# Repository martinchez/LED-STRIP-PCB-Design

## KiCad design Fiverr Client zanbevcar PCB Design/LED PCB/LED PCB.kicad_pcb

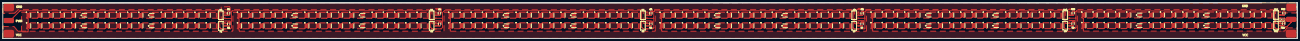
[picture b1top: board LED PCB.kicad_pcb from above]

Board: 2 copper layers, 980.4 x 27.1 mm, 235 parts (0 on the bottom side), 219 nets.

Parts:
J1, J3, J4, J6: Conn_01x01; power pad
J2, J5: Conn_01x01; signal pad
LED1, LED2, LED3, LED4, LED5, LED6, LED7, LED8, LED9, LED10, LED11, LED12, LED13, LED14, LED16, LED17, LED18, LED19, LED20, LED21, LED22, LED23, LED24, LED25, LED26, LED27, LED28, LED29, LED30, LED31, LED32, LED33, LED34, LED35, LED36, LED37, LED38, LED39, LED40, LED41, LED42, LED43, LED44, LED45, LED46, LED47, LED48, LED49, LED50, LED51, LED52, LED53, LED54, LED55, LED56, LED57, LED58, LED59, LED60, LED73, LED74, LED75, LED76, LED77, LED78, LED79, LED80, LED81, LED82, LED83, LED84, LED85, LED86, LED87, LED88, LED89, LED90, LED91, LED92, LED93, LED94, LED95, LED96, LED97, LED98, LED99, LED100, LED101, LED102, LED103, LED104, LED105, LED106, LED107, LED108, LED109, LED110, LED111, LED112, LED113, LED114, LED115, LED116, LED117, LED118, LED119, LED120, LED121, LED122, LED123, LED124, LED125, LED126, LED127, LED128, LED129, LED130, LED131, LED132, LED145, LED146, LED147, LED148, LED149, LED150, LED151, LED152, LED153, LED154, LED155, LED156, LED157, LED158, LED159, LED160, LED161, LED162, LED163, LED164, LED165, LED166, LED167, LED168, LED169, LED170, LED171, LED172, LED173, LED174, LED175, LED176, LED177, LED178, LED179, LED180, LED181, LED182, LED183, LED184, LED185, LED186, LED187, LED188, LED189, LED190, LED191, LED192, LED193, LED194, LED195, LED196, LED197, LED198, LED199, LED200, LED201, LED202, LED203, LED204: SPMWHD32AMH5XAU5SL
LED61, LED62, LED63, LED64, LED65, LED66, LED67, LED68, LED69, LED70, LED71, LED72, LED133, LED134, LED135, LED136, LED137, LED138, LED139, LED140, LED141, LED142, LED143, LED144: L1SP-DRD0002800000
LEDe: SPMWHD32AMH5XAU5SL
R1, R2, R3, R4, R5, R6, R7, R8, R9, R10, R11, R12: 5.6R; R_1206_3216Metric
U1, U2, U3, U4, U5, U6, U7, U8, U9, U10, U11, U12: NCR321ZX
kibuzzard-6473B6E2: G***; kibuzzard-6473B6E2

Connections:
GND: J3.1, J6.1, R1.2, R2.2, R3.2, R4.2, R5.2, R6.2, R7.2, R8.2, R9.2, R10.2, R11.2, R12.2, U1.3 (GND), U2.3 (GND), U3.3 (GND), U4.3 (GND), U5.3 (GND), U6.3 (GND), U7.3 (GND), U8.3 (GND), U9.3 (GND), U10.3 (GND), U11.3 (GND), U12.3 (GND)
unnamed: LED1.2, LED13.1
unnamed: LED10.2, LED22.1
unnamed: LED11.2, LED23.1
unnamed: LED12.2, LED24.1
unnamed: LED13.2, LED25.1
unnamed: LED2.2, LED14.1
unnamed: LED14.2, LED26.1
unnamed: LED3.2, LEDe.1
unnamed: LED27.1, LEDe.2
unnamed: LED4.2, LED16.1
unnamed: LED16.2, LED28.1
unnamed: LED5.2, LED17.1
unnamed: LED17.2, LED29.1
unnamed: LED6.2, LED18.1
unnamed: LED18.2, LED30.1
unnamed: LED7.2, LED19.1
unnamed: LED19.2, LED31.1
unnamed: LED8.2, LED20.1
unnamed: LED20.2, LED32.1
unnamed: LED9.2, LED21.1
unnamed: LED21.2, LED33.1
unnamed: LED22.2, LED34.1
unnamed: LED23.2, LED35.1
unnamed: LED24.2, LED36.1
unnamed: LED25.2, LED37.1
unnamed: LED26.2, LED38.1
unnamed: LED27.2, LED39.1
unnamed: LED28.2, LED40.1
unnamed: LED29.2, LED41.1
unnamed: LED30.2, LED42.1
unnamed: LED31.2, LED43.1
unnamed: LED32.2, LED44.1
unnamed: LED33.2, LED45.1
unnamed: LED34.2, LED46.1
unnamed: LED35.2, LED47.1
unnamed: LED36.2, LED48.1
unnamed: LED37.2, LED49.1
unnamed: LED38.2, LED50.1
unnamed: LED39.2, LED51.1
unnamed: LED40.2, LED52.1
unnamed: LED41.2, LED53.1
unnamed: LED42.2, LED54.1
unnamed: LED43.2, LED55.1
unnamed: LED44.2, LED56.1
unnamed: LED45.2, LED57.1
unnamed: LED46.2, LED58.1
unnamed: LED47.2, LED59.1
unnamed: LED48.2, LED60.1
unnamed: LED49.2, LED61.2
unnamed: LED50.2, LED62.2
unnamed: LED51.2, LED63.2
unnamed: LED52.2, LED64.2
unnamed: LED53.2, LED65.2
unnamed: LED54.2, LED66.2
unnamed: LED55.2, LED67.2
unnamed: LED56.2, LED68.2
unnamed: LED57.2, LED69.2
unnamed: LED58.2, LED70.2
unnamed: LED59.2, LED71.2
unnamed: LED60.2, LED72.2
unnamed: LED61.1, LED73.1
unnamed: LED62.1, LED74.1
unnamed: LED63.1, LED75.1
unnamed: LED64.1, LED76.1
unnamed: LED65.1, LED77.1
unnamed: LED66.1, LED78.1
unnamed: LED67.1, LED79.1
unnamed: LED68.1, LED80.1
unnamed: LED69.1, LED81.1
unnamed: LED70.1, LED82.1
unnamed: LED71.1, LED83.1
unnamed: LED72.1, LED84.1
unnamed: LED73.2, LED85.1
unnamed: LED74.2, LED86.1
unnamed: LED75.2, LED87.1
unnamed: LED76.2, LED88.1
unnamed: LED77.2, LED89.1
unnamed: LED78.2, LED90.1
unnamed: LED79.2, LED91.1
unnamed: LED80.2, LED92.1
unnamed: LED81.2, LED93.1
unnamed: LED82.2, LED94.1
unnamed: LED83.2, LED95.1
unnamed: LED84.2, LED96.1
unnamed: LED85.2, LED97.1
unnamed: LED86.2, LED98.1
unnamed: LED87.2, LED99.1
unnamed: LED88.2, LED100.1
unnamed: LED100.2, LED112.1
unnamed: LED89.2, LED101.1
unnamed: LED101.2, LED113.1
unnamed: LED90.2, LED102.1
unnamed: LED102.2, LED114.1
unnamed: LED91.2, LED103.1
unnamed: LED103.2, LED115.1
unnamed: LED92.2, LED104.1
unnamed: LED104.2, LED116.1
unnamed: LED93.2, LED105.1
unnamed: LED105.2, LED117.1
unnamed: LED94.2, LED106.1
unnamed: LED106.2, LED118.1
unnamed: LED95.2, LED107.1
unnamed: LED107.2, LED119.1
unnamed: LED96.2, LED108.1
unnamed: LED108.2, LED120.1
unnamed: LED97.2, LED109.1
unnamed: LED109.2, LED121.1
unnamed: LED98.2, LED110.1
unnamed: LED110.2, LED122.1
unnamed: LED99.2, LED111.1
unnamed: LED111.2, LED123.1
unnamed: LED112.2, LED124.1
unnamed: LED113.2, LED125.1
unnamed: LED114.2, LED126.1
unnamed: LED115.2, LED127.1
unnamed: LED116.2, LED128.1
unnamed: LED117.2, LED129.1
unnamed: LED118.2, LED130.1
unnamed: LED119.2, LED131.1
unnamed: LED120.2, LED132.1
unnamed: LED121.2, LED133.2
unnamed: LED122.2, LED134.2
unnamed: LED123.2, LED135.2
unnamed: LED124.2, LED136.2
unnamed: LED125.2, LED137.2
unnamed: LED126.2, LED138.2
unnamed: LED127.2, LED139.2
unnamed: LED128.2, LED140.2
unnamed: LED129.2, LED141.2
unnamed: LED130.2, LED142.2
unnamed: LED131.2, LED143.2
unnamed: LED132.2, LED144.2
unnamed: LED133.1, LED145.1
unnamed: LED134.1, LED146.1
unnamed: LED135.1, LED147.1
unnamed: LED136.1, LED148.1
unnamed: LED137.1, LED149.1
unnamed: LED138.1, LED150.1
unnamed: LED139.1, LED151.1
unnamed: LED140.1, LED152.1
unnamed: LED141.1, LED153.1
unnamed: LED142.1, LED154.1
unnamed: LED143.1, LED155.1
unnamed: LED144.1, LED156.1
unnamed: LED145.2, LED157.1
unnamed: LED146.2, LED158.1
unnamed: LED147.2, LED159.1
unnamed: LED148.2, LED160.1
unnamed: LED149.2, LED161.1
unnamed: LED150.2, LED162.1
unnamed: LED151.2, LED163.1
unnamed: LED152.2, LED164.1
unnamed: LED153.2, LED165.1
unnamed: LED154.2, LED166.1
unnamed: LED155.2, LED167.1
unnamed: LED156.2, LED168.1
unnamed: LED157.2, LED169.1
unnamed: LED158.2, LED170.1
unnamed: LED159.2, LED171.1
unnamed: LED160.2, LED172.1
unnamed: LED161.2, LED173.1
unnamed: LED162.2, LED174.1
unnamed: LED163.2, LED175.1
unnamed: LED164.2, LED176.1
unnamed: LED165.2, LED177.1
unnamed: LED166.2, LED178.1
unnamed: LED167.2, LED179.1
unnamed: LED168.2, LED180.1
unnamed: LED169.2, LED181.1
unnamed: LED170.2, LED182.1
unnamed: LED171.2, LED183.1
unnamed: LED172.2, LED184.1
unnamed: LED173.2, LED185.1
unnamed: LED174.2, LED186.1
unnamed: LED175.2, LED187.1
unnamed: LED176.2, LED188.1
unnamed: LED177.2, LED189.1
unnamed: LED178.2, LED190.1
unnamed: LED179.2, LED191.1
unnamed: LED180.2, LED192.1
unnamed: LED181.2, LED193.1
unnamed: LED182.2, LED194.1
unnamed: LED183.2, LED195.1
unnamed: LED184.2, LED196.1
unnamed: LED185.2, LED197.1
unnamed: LED186.2, LED198.1
unnamed: LED187.2, LED199.1
unnamed: LED188.2, LED200.1
unnamed: LED189.2, LED201.1
unnamed: LED190.2, LED202.1
unnamed: LED191.2, LED203.1
unnamed: LED192.2, LED204.1
unnamed: LED193.2, U1.4 (IOUT)
unnamed: LED194.2, U2.4 (IOUT)
unnamed: LED195.2, U3.4 (IOUT)
unnamed: LED196.2, U4.4 (IOUT)
unnamed: LED197.2, U5.4 (IOUT)
unnamed: LED198.2, U6.4 (IOUT)
unnamed: LED199.2, U7.4 (IOUT)
unnamed: LED200.2, U8.4 (IOUT)
unnamed: LED201.2, U9.4 (IOUT)
unnamed: LED202.2, U10.4 (IOUT)
unnamed: LED203.2, U11.4 (IOUT)
unnamed: LED204.2, U12.4 (IOUT)
unnamed: R1.1, U1.2 (REXT)
unnamed: R2.1, U2.2 (REXT)
unnamed: R3.1, U3.2 (REXT)
unnamed: R4.1, U4.2 (REXT)
unnamed: R5.1, U5.2 (REXT)
unnamed: R6.1, U6.2 (REXT)
unnamed: R7.1, U7.2 (REXT)
unnamed: R8.1, U8.2 (REXT)
unnamed: R9.1, U9.2 (REXT)
unnamed: R10.1, U10.2 (REXT)
unnamed: R11.1, U11.2 (REXT)
unnamed: R12.1, U12.2 (REXT)
PWM: J2.1, J5.1, U1.1 (VEN), U2.1 (VEN), U3.1 (VEN), U4.1 (VEN), U5.1 (VEN), U6.1 (VEN), U7.1 (VEN), U8.1 (VEN), U9.1 (VEN), U10.1 (VEN), U11.1 (VEN), U12.1 (VEN)
VCC: J1.1, J4.1, LED1.1, LED2.1, LED3.1, LED4.1, LED5.1, LED6.1, LED7.1, LED8.1, LED9.1, LED10.1, LED11.1, LED12.1

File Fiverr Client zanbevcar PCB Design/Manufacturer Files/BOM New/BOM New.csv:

Comment,Designator,Footprint,Manufacturer Part Number,Digikey Link,Qty
Conn_01x01,"    J2, J5",PCB Footprints:signal pad,-,-,2
Conn_01x01,"    J1, J3, J4, J6",PCB Footprints:power pad,-,-,4
L1SP-DRD0002800000,"    LED61-LED72, LED133-LED144",PCB Footprints:L1SP-DRD0002800000,L1SP-DRD0002800000,https://www.digikey.si/en/products/detail/lumileds/L1SP-DRD0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,24
SPMWHD32AMH5XAU5SL,"    LED1-LED60, LED73-LED132, LED145-LED204",PCB Footprints:SPMWHD32AMH5XAU5SL,SPMWHD32AMH5XAU5SL,https://www.digikey.si/en/products/detail/samsung-semiconduc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,180
5.6R,    R1-R12,Resistor_SMD:R_1206_3216Metric,RMCF1206FT5R60,https://www.digikey.si/en/products/detail/stackpole-electron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,12
NCR321ZX,    U1-U12,PCB Footprints:NCR321ZX,NCR321ZX,https://www.digikey.si/en/products/detail/nexperia-usa-inc/N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,12
"U1, U2, U3, U4, U5, U6, U7, U8, U9, U10, U11, U12",12,NCR321ZX,NCR321ZX,PCB Footprints:NCR321ZX,
